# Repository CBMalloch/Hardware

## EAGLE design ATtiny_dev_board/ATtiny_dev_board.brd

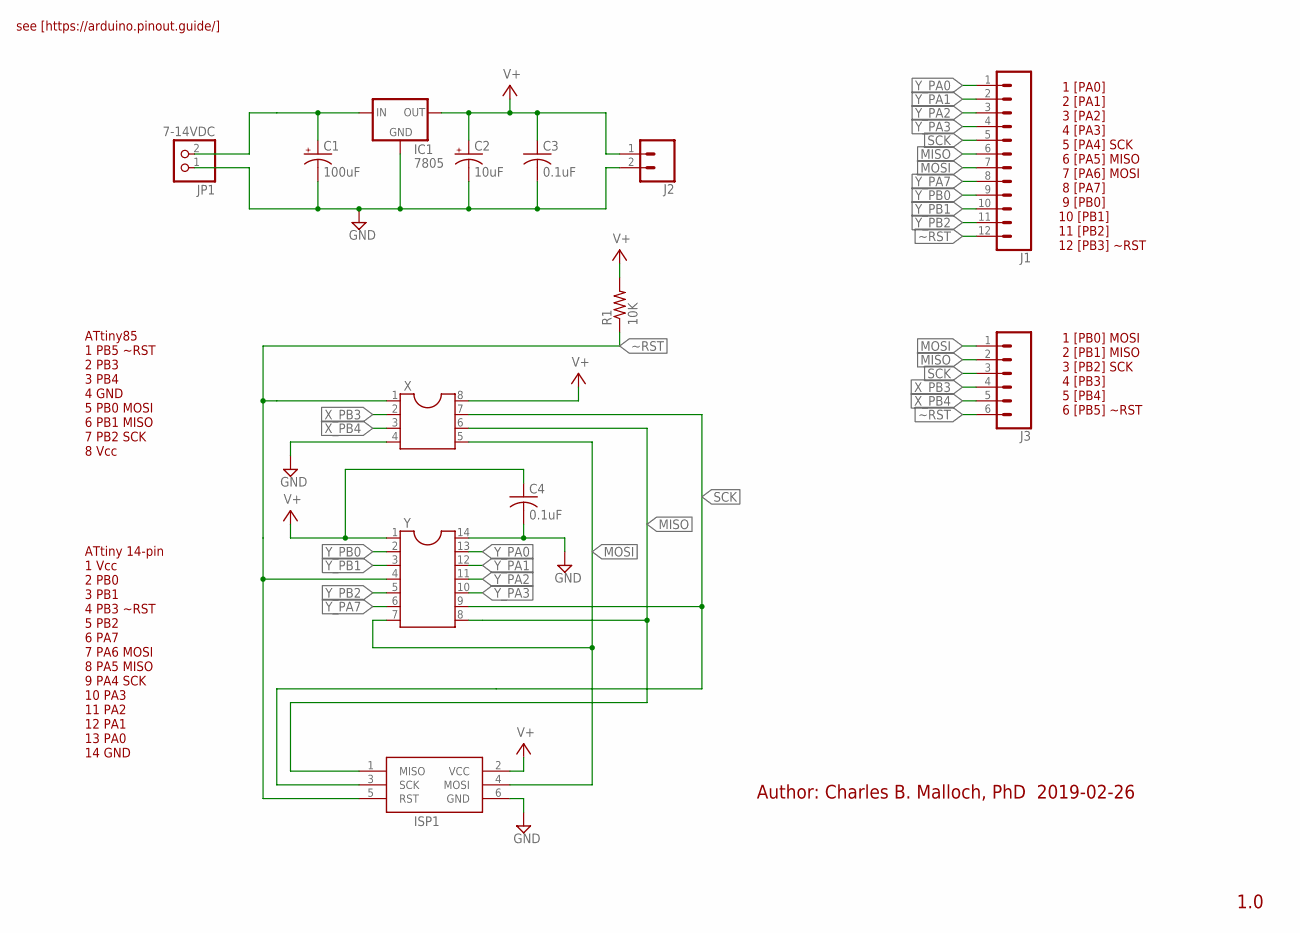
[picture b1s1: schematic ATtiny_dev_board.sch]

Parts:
C1: 100uF; TT2D7
C2: 10uF; E1,8-4
C3, C4: 0.1uF; C025-025X050
IC1: 7805; TO-220-ALT
ISP1: AVRISP-BOX
J1: CONN_12LOCK_LONGPADS; 1X12_LOCK_LONGPADS
J2: CONN_02LOCK_LONGPADS; 1X02_LOCK_LONGPADS
J3: CONN_06LOCK_LONGPADS; 1X06_LOCK_LONGPADS
JP1: 7-14VDC; 1X02
R1: 10K; 0309/12
X: DIL8S; SOCKET-08
Y: DIL14S; SOCKET-14

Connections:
5VDC: C2.+, C3.1, C4.1, IC1.OUT, ISP1.2 (VCC), J2.1, R1.2, X.8, Y.1
GND: C1.-, C2.-, C3.2, C4.2, IC1.GND, ISP1.6 (GND), J2.2, JP1.1, X.4, Y.14
MISO: ISP1.1 (MISO), J1.6, J3.2, X.6, Y.8
MOSI: ISP1.4 (MOSI), J1.7, J3.1, X.5, Y.7
SCK: ISP1.3 (SCK), J1.5, J3.3, X.7, Y.9
VIN: C1.+, IC1.IN, JP1.2
X_PB3: J3.4, X.2
X_PB4: J3.5, X.3
Y_PA0: J1.1, Y.13
Y_PA1: J1.2, Y.12
Y_PA2: J1.3, Y.11
Y_PA3: J1.4, Y.10
Y_PA7: J1.8, Y.6
Y_PB0: J1.9, Y.2
Y_PB1: J1.10, Y.3
Y_PB2: J1.11, Y.5
~RST: ISP1.5 (RST), J1.12, J3.6, R1.1, X.1, Y.4

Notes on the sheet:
Author: Charles B. Malloch, PhD 2019-02-26
1.0
ATtiny85 1 PB5 ~RST 2 PB3 3 PB4 4 GND 5 PB0 MOSI 6 PB1 MISO 7 PB2 SCK 8 Vcc
see [https://arduino.pinout.guide/]
ATtiny 14-pin 1 Vcc 2 PB0 3 PB1 4 PB3 ~RST 5 PB2 6 PA7 7 PA6 MOSI 8 PA5 MISO 9 PA4 SCK 10 PA3 11 PA2 12 PA1 13 PA0 14 GND
1 [PB0] MOSI 2 [PB1] MISO 3 [PB2] SCK 4 [PB3] 5 [PB4] 6 [PB5] ~RST
1 [PA0] 2 [PA1] 3 [PA2] 4 [PA3] 5 [PA4] SCK 6 [PA5] MISO 7 [PA6] MOSI 8 [PA7] 9 [PB0] 10 [PB1] 11 [PB2] 12 [PB3] ~RST

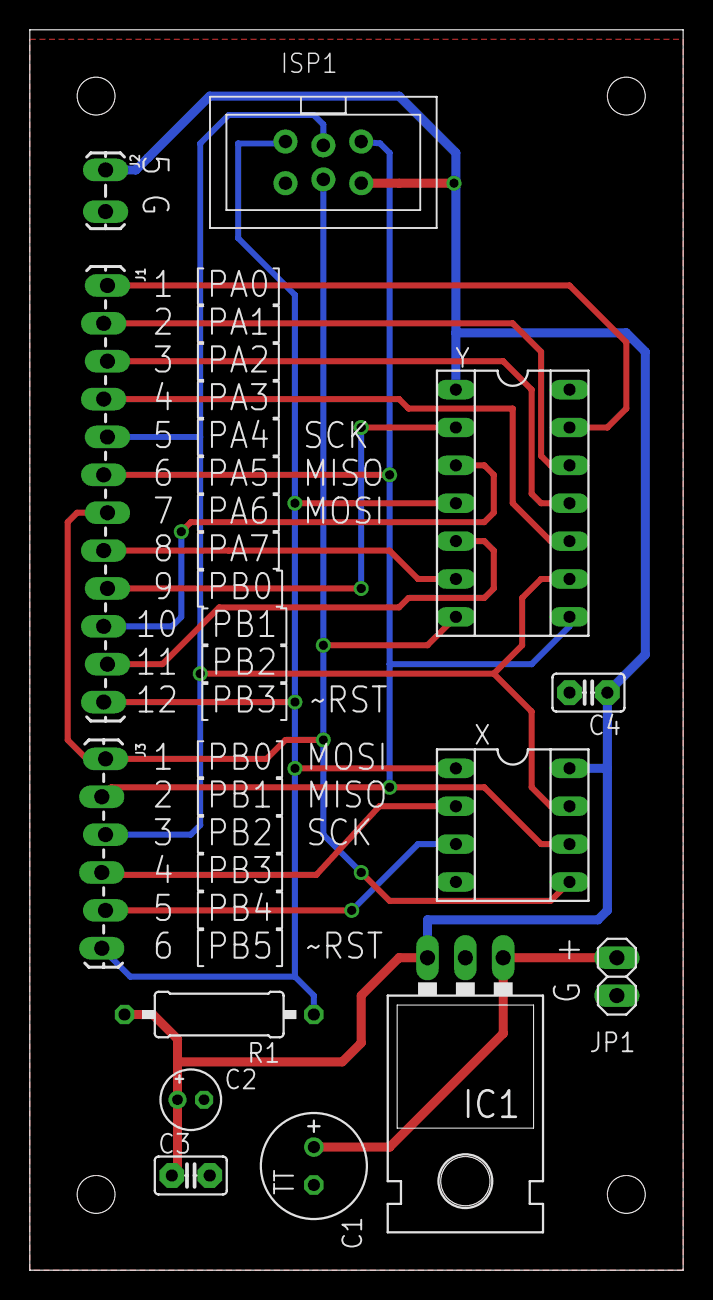
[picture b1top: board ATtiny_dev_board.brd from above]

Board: 2 copper layers, 43.8 x 83.2 mm, 13 parts (0 on the bottom side), 17 nets.

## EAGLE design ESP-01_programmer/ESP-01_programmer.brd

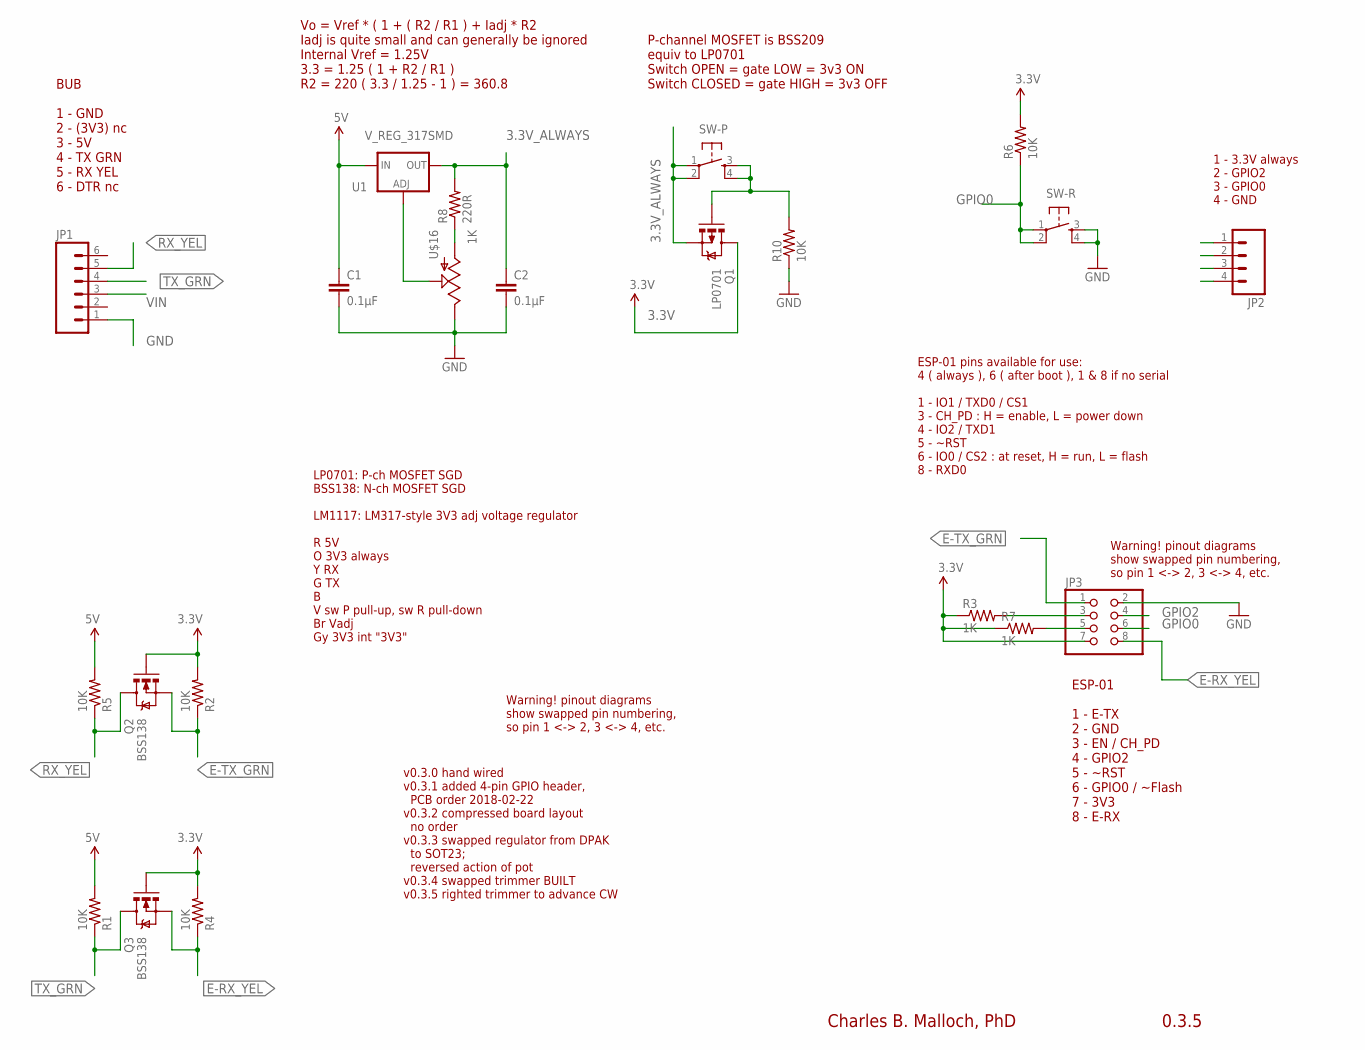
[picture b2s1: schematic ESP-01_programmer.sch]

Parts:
C1, C2: 0.1µF; 1206
JP1: M06LOCK_LONGPADS; 1X06_LOCK_LONGPADS
JP2: M04LOCK_LONGPADS; 1X04_LOCK_LONGPADS
JP3: PINHD-2X4; 2X04
Q1: LP0701; SOT23-3
Q2, Q3: BSS138; SOT23-3
R1, R2, R4, R5, R6, R10: 10K; 1206
R3, R7: 1K; 1206
R8: 220R; 1206
SW-P: TAC_SWITCHPTH; TACTILE-PTH
SW-R: TAC_SWITCHPTH; TACTILE-PTH
U1: V_REG_317SMD; SOT223
U$16: 1K; 3362U

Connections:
3.3V: JP3.7, Q1.3 (D), Q2.1 (G), Q3.1 (G), R2.2, R3.1, R4.2, R6.2, R7.1
3.3V_ALWAYS: C2.1, JP2.1, Q1.2 (S), R8.2, SW-P.1, SW-P.2, U1.2 (OUT)
E-RX_YEL: JP3.8, Q3.2 (S), R4.1
E-TX_GRN: JP3.1, Q2.2 (S), R2.1
GND: C1.2, C2.2, JP1.1, JP2.4, JP3.2, R10.1, SW-R.3, SW-R.4, U$16.P$1 (E)
GPIO0: JP2.3, JP3.6, R6.1, SW-R.1, SW-R.2
GPIO2: JP2.2, JP3.4
unnamed: JP3.3, R3.2
unnamed: JP3.5, R7.2
unnamed: R8.1, U$16.P$3 (A)
unnamed: U1.1 (ADJ), U$16.P$2 (S)
unnamed: Q1.1 (G), R10.2, SW-P.3, SW-P.4
RX_YEL: JP1.5, Q2.3 (D), R5.1
TX_GRN: JP1.4, Q3.3 (D), R1.1
VIN: C1.1, JP1.3, R1.2, R5.2, U1.3 (IN)

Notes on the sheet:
BUB 1 - GND 2 - (3V3) nc 3 - 5V 4 - TX GRN 5 - RX YEL 6 - DTR nc
Charles B. Malloch, PhD
0.3.5
ESP-01 1 - E-TX 2 - GND 3 - EN / CH_PD 4 - GPIO2 5 - ~RST 6 - GPIO0 / ~Flash 7 - 3V3 8 - E-RX
LP0701: P-ch MOSFET SGD BSS138: N-ch MOSFET SGD LM1117: LM317-style 3V3 adj voltage regulator R 5V O 3V3 always Y RX G TX B V sw P pull-up, sw R pull-down Br Vadj Gy 3V3 int "3V3"
ESP-01 pins available for use: 4 ( always ), 6 ( after boot ), 1 & 8 if no serial 1 - IO1 / TXD0 / CS1 3 - CH_PD : H = enable, L = power down 4 - IO2 / TXD1 5 - ~RST 6 - IO0 / CS2 : at reset, H = run, L = flash 8 - RXD0
1 - 3.3V always 2 - GPIO2 3 - GPIO0 4 - GND
v0.3.0 hand wired v0.3.1 added 4-pin GPIO header, PCB order 2018-02-22 v0.3.2 compressed board layout no order v0.3.3 swapped regulator from DPAK to SOT23; reversed action of pot v0.3.4 swapped trimmer BUILT v0.3.5 righted trimmer to advance CW
P-channel MOSFET is BSS209 equiv to LP0701 Switch OPEN = gate LOW = 3v3 ON Switch CLOSED = gate HIGH = 3v3 OFF
Warning! pinout diagrams show swapped pin numbering, so pin 1 <-> 2, 3 <-> 4, etc.
Vo = Vref * ( 1 + ( R2 / R1 ) + Iadj * R2 Iadj is quite small and can generally be ignored Internal Vref = 1.25V 3.3 = 1.25 ( 1 + R2 / R1 ) R2 = 220 ( 3.3 / 1.25 - 1 ) = 360.8

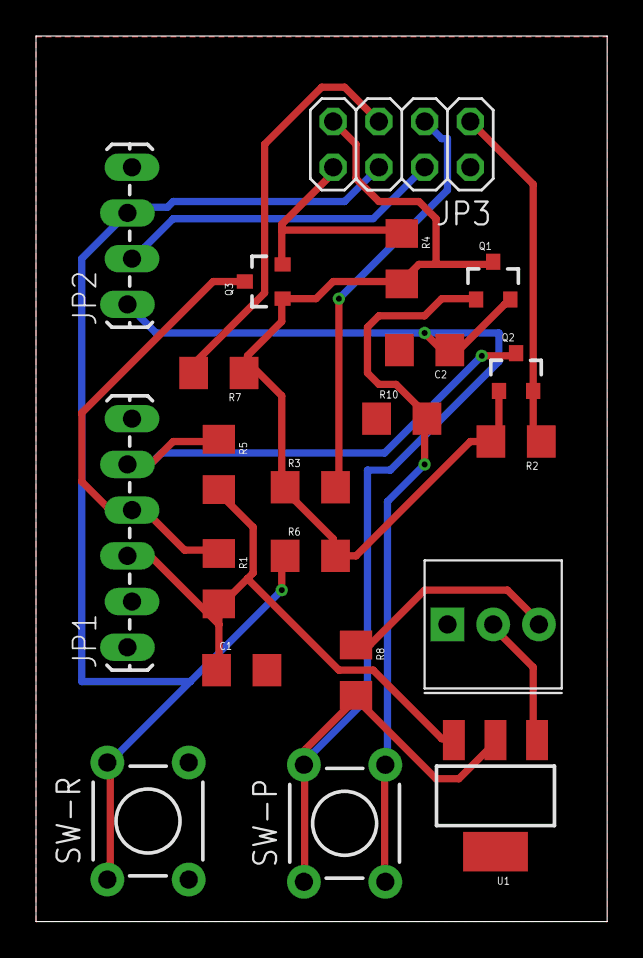
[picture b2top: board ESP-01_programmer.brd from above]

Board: 2 copper layers, 31.7 x 49.2 mm, 21 parts (0 on the bottom side), 15 nets.

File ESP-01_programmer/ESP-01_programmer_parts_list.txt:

Partlist exported from /Users/chuck/Documents/Develop/eagle/ESP-01_programmer/ESP-01_programmer.sch at 2018-02-24 10:13 AM

Part Value          Device             Package            Description       PROD_ID     VALUE 
C1   0.1µF          CAP1206            1206               Capacitor                           
C2   0.1µF          CAP1206            1206               Capacitor                           
JP1                 M06LOCK_LONGPADS   1X06_LOCK_LONGPADS Header 6                            
JP2                 M04LOCK_LONGPADS   1X04_LOCK_LONGPADS Header 4                            
JP3                 PINHD-2X4          2X04               PIN HEADER                          
Q1   LP0701         MOSFET-PCHANNELSMD SOT23-3            Generic PMOSFET                     
Q2   BSS138         BSS138TRANS-00830  SOT23-3            NMOSFET, Enh Mode TRANS-00830 BSS138
Q3   BSS138         BSS138TRANS-00830  SOT23-3            NMOSFET, Enh Mode TRANS-00830 BSS138
R1   10K            RESISTOR1206       1206               Resistor                            
R2   10K            RESISTOR1206       1206               Resistor                            
R3   1K             RESISTOR1206       1206               Resistor                            
R4   10K            RESISTOR1206       1206               Resistor                            
R5   10K            RESISTOR1206       1206               Resistor                            
R6   10K            RESISTOR1206       1206               Resistor                            
R7   1K             RESISTOR1206       1206               Resistor                            
R8   220R           RESISTOR1206       1206               Resistor                            
R10  10K            RESISTOR1206       1206               Resistor                            
SW-P                TAC_SWITCHPTH      TACTILE-PTH        Momentary Switch                    
SW-R                TAC_SWITCHPTH      TACTILE-PTH        Momentary Switch                    
U$16 100R           POT                ALPS_POT                                               
U1   V_REG_317DPACK V_REG_317DPACK     V-REG_DPACK        Voltage Regulator

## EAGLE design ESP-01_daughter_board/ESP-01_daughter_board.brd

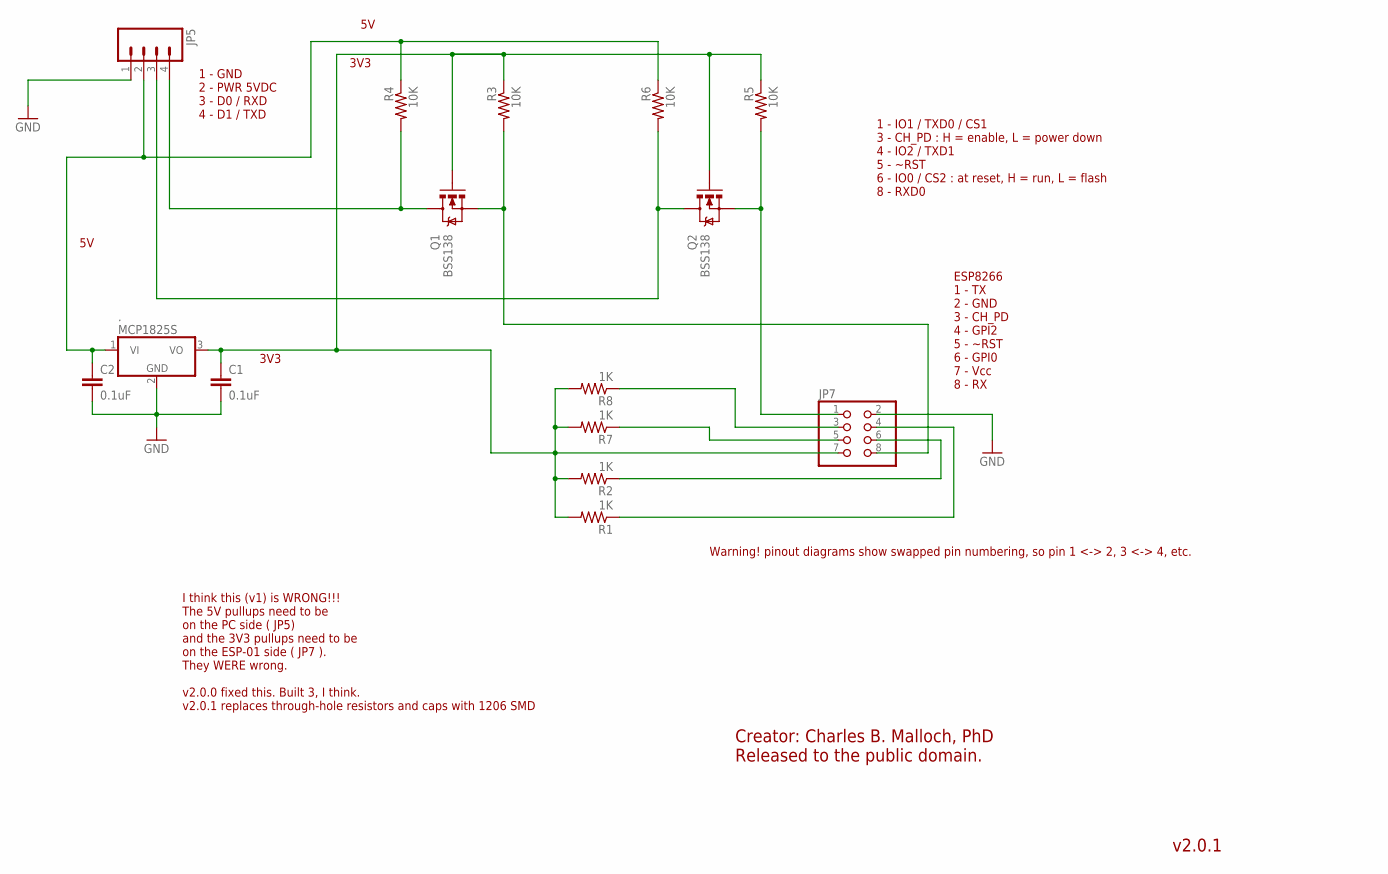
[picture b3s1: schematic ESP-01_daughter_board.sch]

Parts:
.: MCP1825S; SOT223
C1, C2: 0.1uF; C1206
JP5: M04LOCK_LONGPADS; 1X04_LOCK_LONGPADS
JP7: PINHD-2X4; 2X04
Q1, Q2: BSS138; SOT23-3
R1, R2, R7, R8: 1K; M1206
R3, R4, R5, R6: 10K; 1206

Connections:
3V3: ..3 (VO), C1.1, JP7.7, Q1.1 (G), Q2.1 (G), R1.2, R2.2, R3.1, R5.1, R7.2, R8.2
5V: ..1 (VI), C2.1, JP5.2, R4.1, R6.1
E-RX: JP7.8, Q1.2 (S), R3.2
E-TX: JP7.1, Q2.2 (S), R5.2
GND: ..2 (GND), C1.2, C2.2, JP5.1, JP7.2
unnamed: JP7.3, R8.1
unnamed: JP7.5, R7.1
unnamed: JP7.6, R2.1
unnamed: JP7.4, R1.1
RX: JP5.3, Q2.3 (D), R6.2
TX: JP5.4, Q1.3 (D), R4.2

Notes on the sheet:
v2.0.1
Creator: Charles B. Malloch, PhD Released to the public domain.
1 - GND 2 - PWR 5VDC 3 - D0 / RXD 4 - D1 / TXD
ESP8266 1 - TX 2 - GND 3 - CH_PD 4 - GPI2 5 - ~RST 6 - GPI0 7 - Vcc 8 - RX
3V3
I think this (v1) is WRONG!!! The 5V pullups need to be on the PC side ( JP5) and the 3V3 pullups need to be on the ESP-01 side ( JP7 ). They WERE wrong. v2.0.0 fixed this. Built 3, I think. v2.0.1 replaces through-hole resistors and caps with 1206 SMD
1 - IO1 / TXD0 / CS1 3 - CH_PD : H = enable, L = power down 4 - IO2 / TXD1 5 - ~RST 6 - IO0 / CS2 : at reset, H = run, L = flash 8 - RXD0
Warning! pinout diagrams show swapped pin numbering, so pin 1 <-> 2, 3 <-> 4, etc.

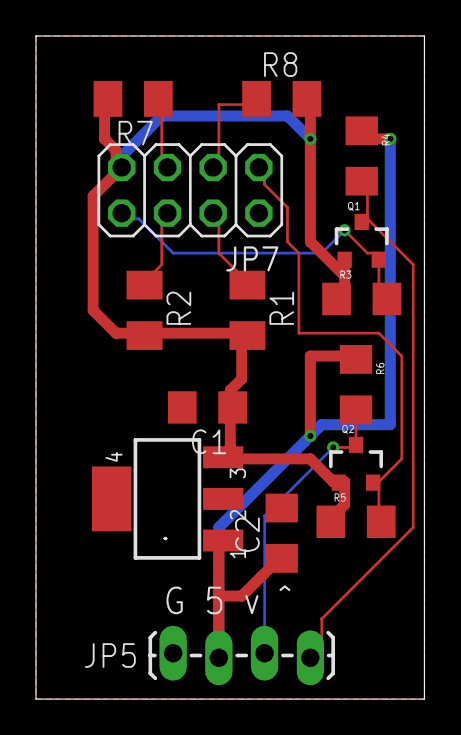
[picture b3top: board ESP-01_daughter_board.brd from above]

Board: 2 copper layers, 21.6 x 36.8 mm, 15 parts (0 on the bottom side), 11 nets.

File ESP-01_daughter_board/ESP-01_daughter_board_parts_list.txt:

Partlist exported from /Users/chuck/Documents/Develop/eagle/ESP-01_daughter_board/ESP-01_daughter_board.sch at 2018-02-24 10:28 AM

Part Value    Device            Package            Description                                      PROD_ID     SPICEMODEL SPICEPREFIX VALUE 
.    MCP1825S MCP1703DB         SOT223             250 mA, 16V, Low Quiescent Current LDO Regulator                                          
C1   0.1uF    CC1206            C1206              CAPACITOR, European symbol                                   NONE       C                 
C2   0.1uF    CC1206            C1206              CAPACITOR, European symbol                                   NONE       C                 
JP5           M04LOCK_LONGPADS  1X04_LOCK_LONGPADS Header 4                                                                                  
JP7           PINHD-2X4         2X04               PIN HEADER                                                                                
Q1   BSS138   BSS138TRANS-00830 SOT23-3            NMOSFET, Enh Mode                                TRANS-00830                        BSS138
Q2   BSS138   BSS138TRANS-00830 SOT23-3            NMOSFET, Enh Mode                                TRANS-00830                        BSS138
R1   1K       R-US_M1206        M1206              RESISTOR, American symbol                                                                 
R2   1K       R-US_M1206        M1206              RESISTOR, American symbol                                                                 
R3   10K      RESISTOR1206      1206               Resistor                                                                                  
R4   10K      RESISTOR1206      1206               Resistor                                                                                  
R5   10K      RESISTOR1206      1206               Resistor                                                                                  
R6   10K      RESISTOR1206      1206               Resistor                                                                                  
R7   1K       R-US_M1206        M1206              RESISTOR, American symbol                                                                 
R8   1K       R-US_M1206        M1206              RESISTOR, American symbol

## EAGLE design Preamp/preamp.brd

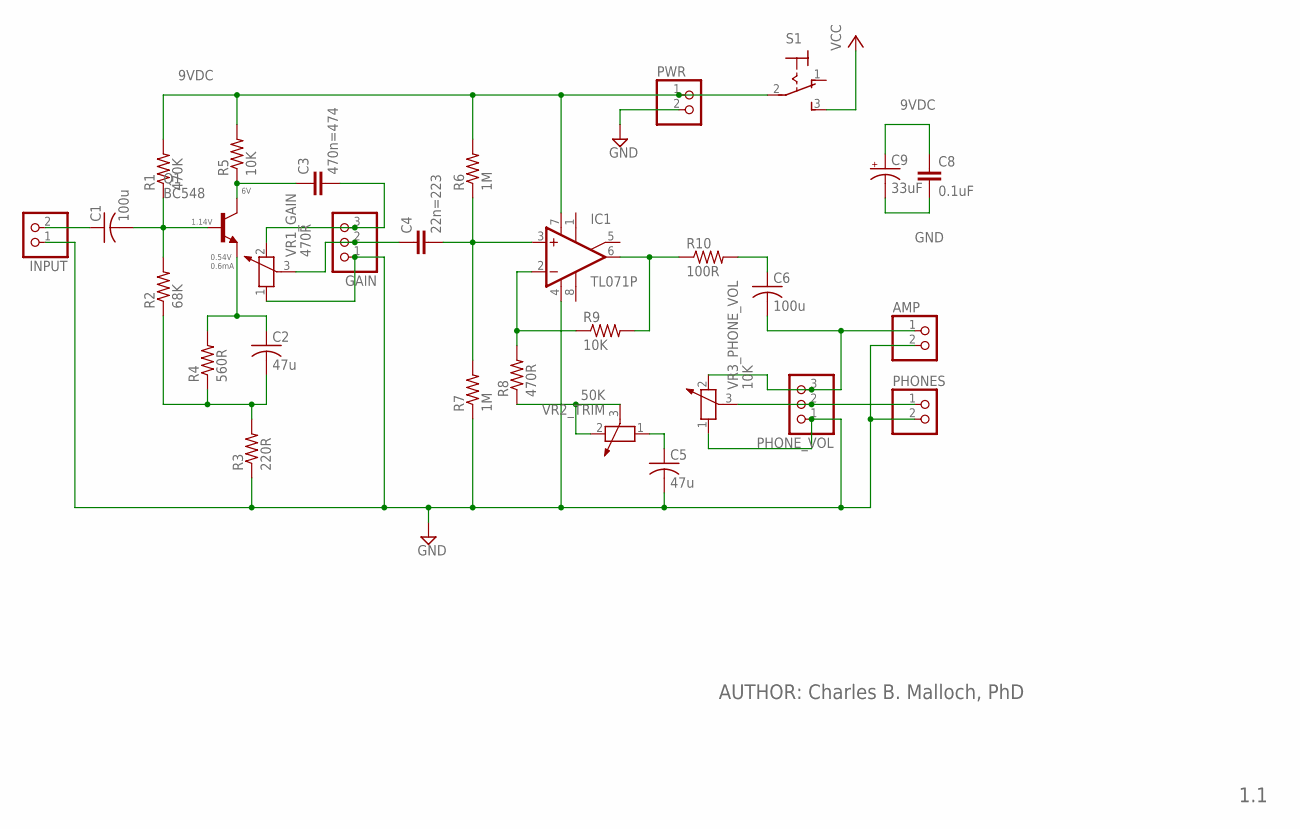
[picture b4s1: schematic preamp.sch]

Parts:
AMP: PINHD-1X2; 1X02
C1, C6: 100u; C025-040X050
C2, C5: 47u; C025-040X050
C3: 470n=474; C025-060X050
C4: 22n=223; C025-060X050
C8: 0.1uF; C025-030X050
C9: 33uF; E5-6
GAIN: PINHD-1X3; 1X03
IC1: TL071P; DIL08
INPUT: PINHD-1X2; 1X02
PHONES: PINHD-1X2; 1X02
PHONE_VOL: PINHD-1X3; 1X03
PWR: PINHD-1X2; 1X02
Q1: BC548; TO92-EBC
R1: 470K; 0204/7
R2: 68K; 0204/7
R3: 220R; 0204/7
R4: 560R; 0204/7
R5, R9: 10K; 0204/7
R6, R7: 1M; 0204/7
R8: 470R; 0204/7
R10: 100R; 0204/7
S1: 320-916
VR1_GAIN: 470R; PT-10
VR2_TRIM: 50K; PT-10
VR3_PHONE_VOL: 10K; PT-10

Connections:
9VDC: C8.1, C9.+, IC1.7 (V+), PWR.1, R1.2, R5.2, R6.2, S1.2
BAT+: S1.3 (S)
GND: AMP.2, C5.2, C8.2, C9.-, GAIN.1, IC1.4 (V-), INPUT.1, PHONES.2, PHONE_VOL.1, PWR.2, R3.1, R7.1, VR1_GAIN.1, VR3_PHONE_VOL.1
unnamed: C4.1, GAIN.2, VR1_GAIN.3
unnamed: C1.1, INPUT.2
unnamed: C1.2, Q1.B, R1.1, R2.2
unnamed: C3.2, GAIN.3, VR1_GAIN.2
unnamed: PHONES.1, PHONE_VOL.2, VR3_PHONE_VOL.3
unnamed: C3.1, Q1.C, R5.1
unnamed: C2.2, R2.1, R3.2, R4.1
unnamed: C4.2, IC1.3 (+IN), R6.1, R7.2
unnamed: C2.1, Q1.E, R4.2
unnamed: IC1.6 (OUT), R9.2, R10.1
unnamed: IC1.2 (-IN), R8.2, R9.1
unnamed: R8.1, VR2_TRIM.2, VR2_TRIM.3
unnamed: C5.1, VR2_TRIM.1
unnamed: C6.1, R10.2
unnamed: AMP.1, C6.2, PHONE_VOL.3, VR3_PHONE_VOL.2

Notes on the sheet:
AUTHOR: Charles B. Malloch, PhD
1.1
1.14V
0.54V 0.6mA

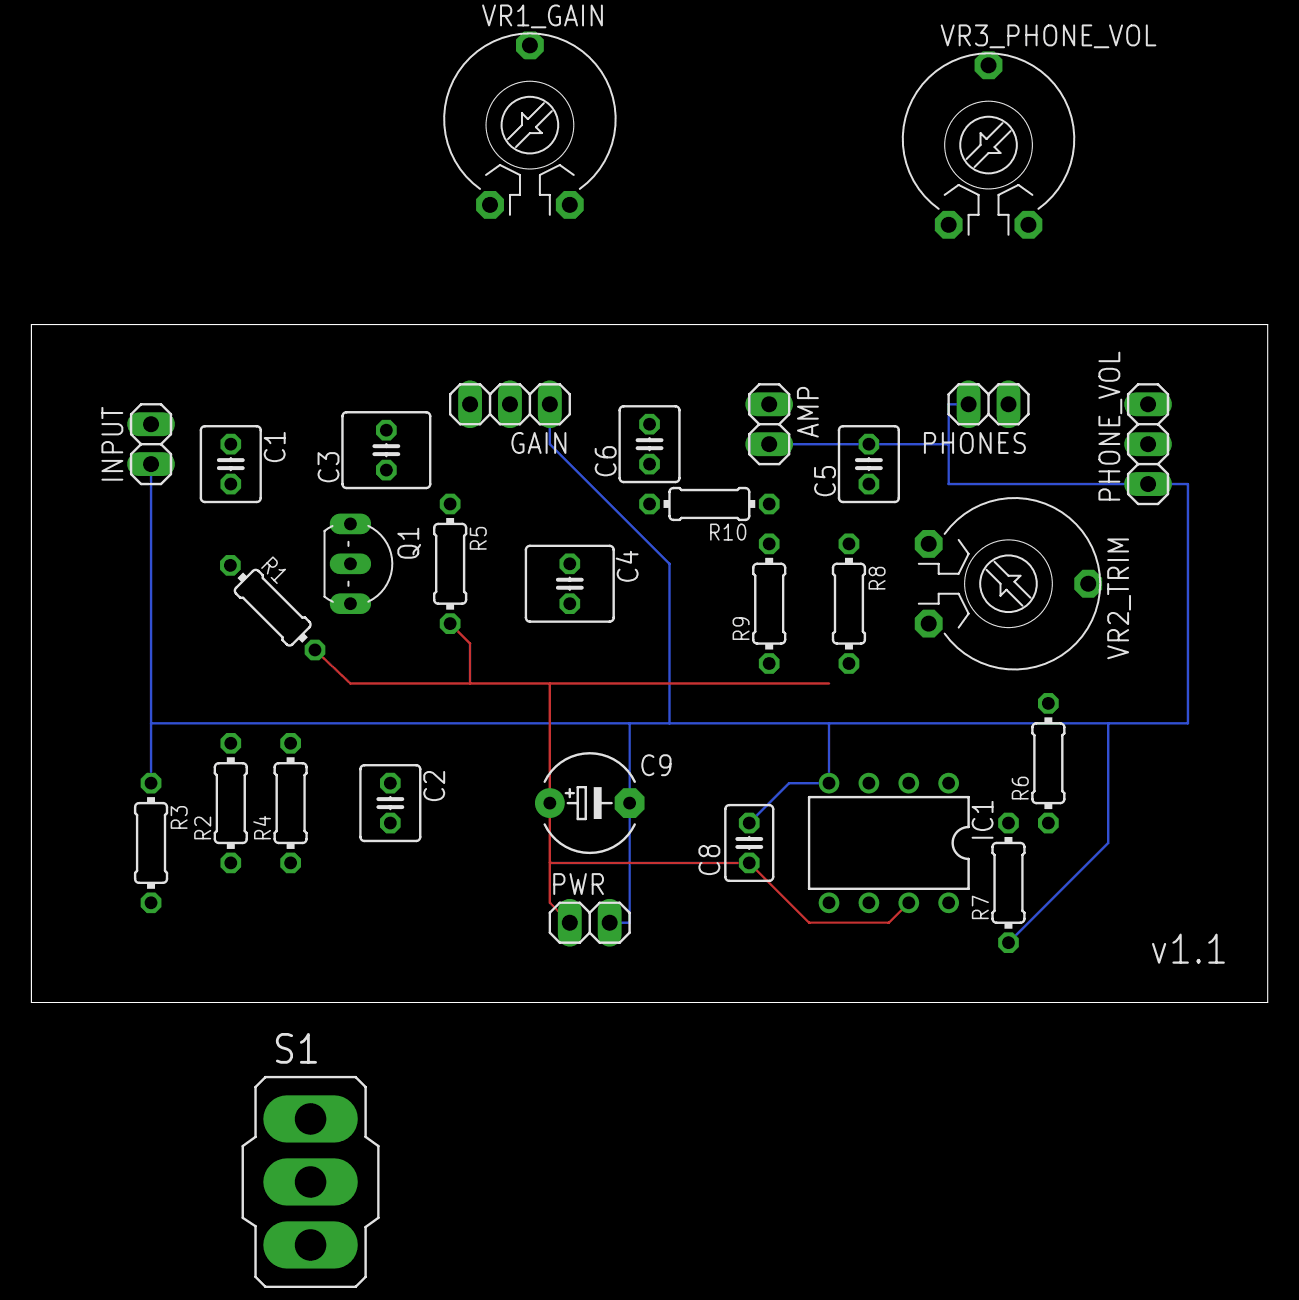
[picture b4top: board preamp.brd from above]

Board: 2 copper layers, 78.7 x 43.2 mm, 30 parts (0 on the bottom side), 17 nets.

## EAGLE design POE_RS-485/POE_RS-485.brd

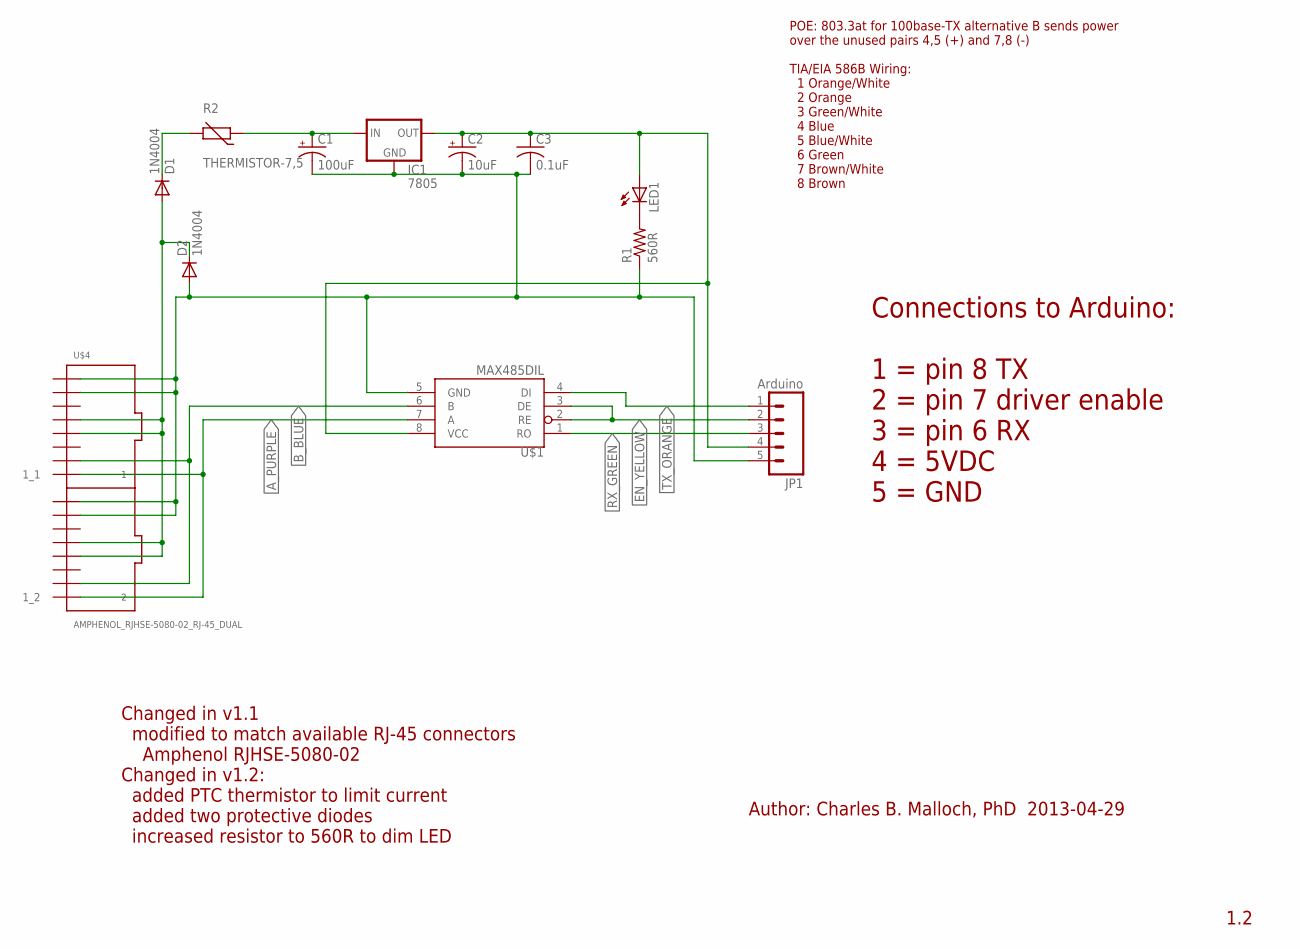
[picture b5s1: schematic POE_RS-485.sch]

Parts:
C1: 100uF; TT2D7
C2: 10uF; E1,8-4
C3: 0.1uF; C025-025X050
D1, D2: 1N4004; DO41-10
IC1: 7805; TO-220-ALT
JP1: Arduino; 1X05_LOCK_LONGPADS
LED1: LED3MM
R1: 560R; 0204/7
R2: THERMISTOR-7,5; R-7,5
U$1: MAX485DIL; DIL08
U$4: AMPHENOL_RJHSE-5080-02_RJ-45_DUAL; AMPHENOL_RJHSE-5080-02

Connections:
A_PURPLE: U$1.7 (A), U$4.TX_D1+_2 (1_2), U$4.TX_DI+_1 (1_1)
B_BLUE: U$1.6 (B), U$4.TX_D1-_2 (2_2), U$4.TX_DI-_1 (2_1)
EN_YELLOW: JP1.2, U$1.2 (RE), U$1.3 (DE)
GND: C1.-, C2.-, C3.2, D2.A, IC1.GND, JP1.5, R1.1, U$1.5 (GND), U$4.POE-_1_1 (7_1), U$4.POE-_1_2 (7_2), U$4.POE-_2_1 (8_1), U$4.POE-_2_2 (8_2)
unnamed: LED1.K (C), R1.2
unnamed: C1.+, IC1.IN, R2.1
unnamed: D1.C, R2.2
PWR: C2.+, C3.1, IC1.OUT, JP1.4, LED1.A, U$1.8 (VCC)
RX_GREEN: JP1.3, U$1.1 (RO)
TX_ORANGE: JP1.1, U$1.4 (DI)
VIN: D1.A, D2.C, U$4.POE+_1_1 (4_1), U$4.POE+_1_2 (4_2), U$4.POE+_2_1 (5_1), U$4.POE+_2_2 (5_2)

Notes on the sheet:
Author: Charles B. Malloch, PhD 2013-04-29
1.2
Connections to Arduino: 1 = pin 8 TX 2 = pin 7 driver enable 3 = pin 6 RX 4 = 5VDC 5 = GND
POE: 803.3at for 100base-TX alternative B sends power over the unused pairs 4,5 (+) and 7,8 (-) TIA/EIA 586B Wiring: 1 Orange/White 2 Orange 3 Green/White 4 Blue 5 Blue/White 6 Green 7 Brown/White 8 Brown
Changed in v1.1 modified to match available RJ-45 connectors Amphenol RJHSE-5080-02 Changed in v1.2: added PTC thermistor to limit current added two protective diodes increased resistor to 560R to dim LED

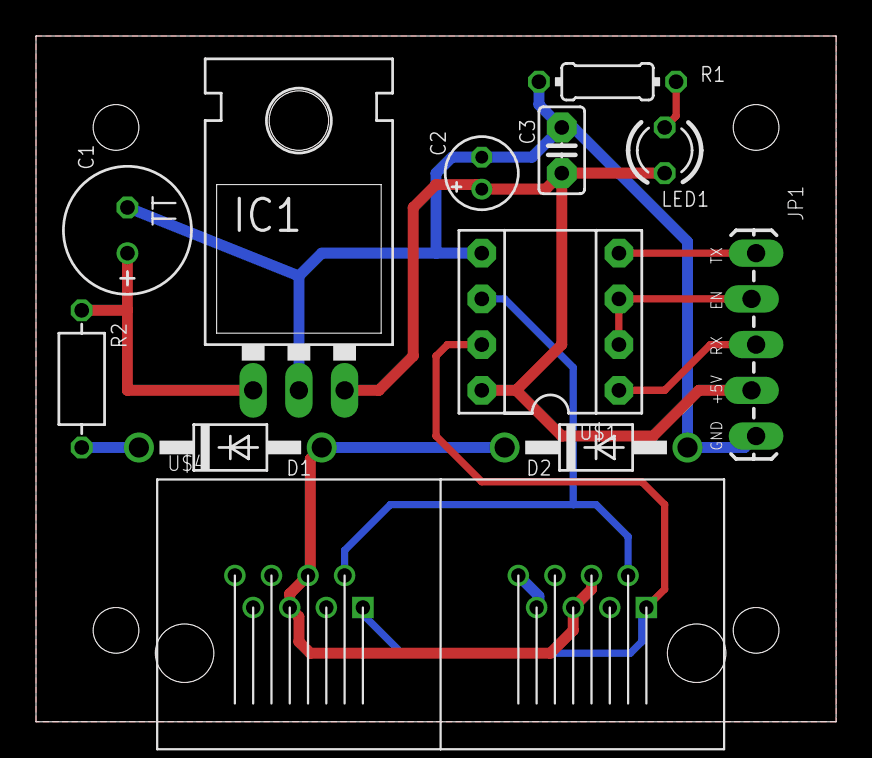
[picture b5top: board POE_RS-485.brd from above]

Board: 2 copper layers, 44.5 x 38.1 mm, 12 parts (0 on the bottom side), 11 nets.

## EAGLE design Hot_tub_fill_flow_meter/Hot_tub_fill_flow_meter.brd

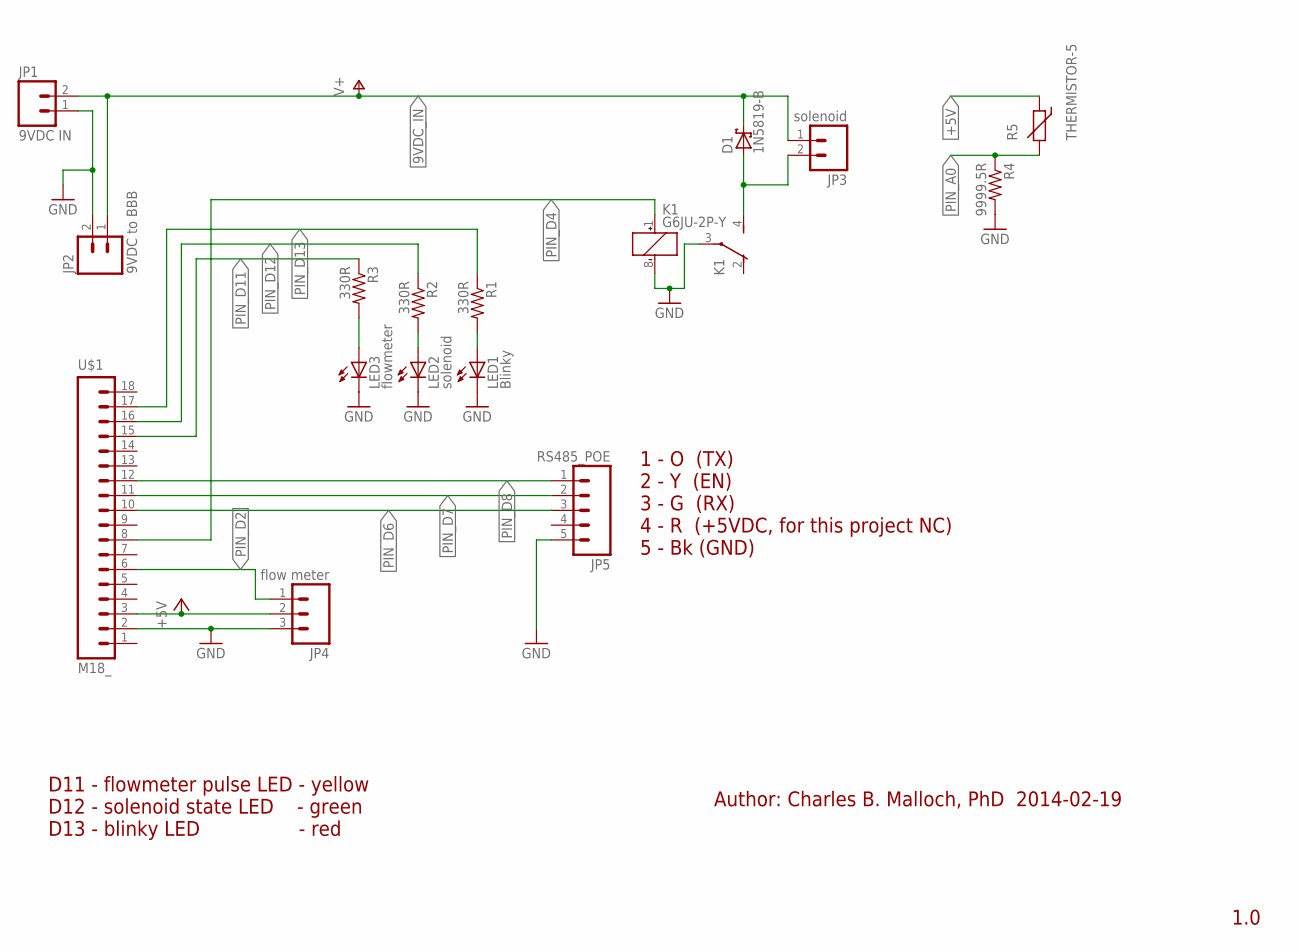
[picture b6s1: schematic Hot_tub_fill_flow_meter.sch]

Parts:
D1: 1N5819-B; DO41-7.6
JP1: 9VDC IN; 1X02_LOCK
JP2: 9VDC to BBB; 1X02_LOCK
JP3: solenoid; 1X02_LOCK
JP4: flow meter; 1X03_LOCK
JP5: RS485_POE; 1X05
K1: G6JU-2P-Y; G6J-2P-Y
LED1: Blinky; LED5MM
LED2: solenoid; LED5MM
LED3: flowmeter; LED5MM
R1, R2, R3: 330R; AXIAL-0.3
R4: 9999.5R; AXIAL-0.3
R5: THERMISTOR-5; R-5
U$1: M18_; 1X18

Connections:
9VDC_IN: D1.C, JP1.2, JP2.1, JP3.1
+5V: JP4.2, R5.1, U$1.3
GND: JP1.1, JP2.2, JP4.3, JP5.5, K1.3, K1.8 (-), LED1.K (C), LED2.K (C), LED3.K (C), R4.P$2 (2), U$1.2
unnamed: LED1.A, R1.P$2 (2)
unnamed: D1.A, JP3.2, K1.4 (S)
unnamed: LED2.A, R2.P$2 (2)
unnamed: LED3.A, R3.P$2 (2)
PIN_A0: R4.P$1 (1), R5.2
PIN_D2: JP4.1, U$1.6
PIN_D4: K1.1 (+), U$1.8
PIN_D6: JP5.3, U$1.10
PIN_D7: JP5.2, U$1.11
PIN_D8: JP5.1, U$1.12
PIN_D11: R3.P$1 (1), U$1.15
PIN_D12: R2.P$1 (1), U$1.16
PIN_D13: R1.P$1 (1), U$1.17

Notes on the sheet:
Author: Charles B. Malloch, PhD 2014-02-19
1.0
D11 - flowmeter pulse LED - yellow D12 - solenoid state LED - green D13 - blinky LED - red
1 - O (TX) 2 - Y (EN) 3 - G (RX) 4 - R (+5VDC, for this project NC) 5 - Bk (GND)

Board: 2 copper layers, 16 parts (0 on the bottom side), 16 nets, no tracks yet.

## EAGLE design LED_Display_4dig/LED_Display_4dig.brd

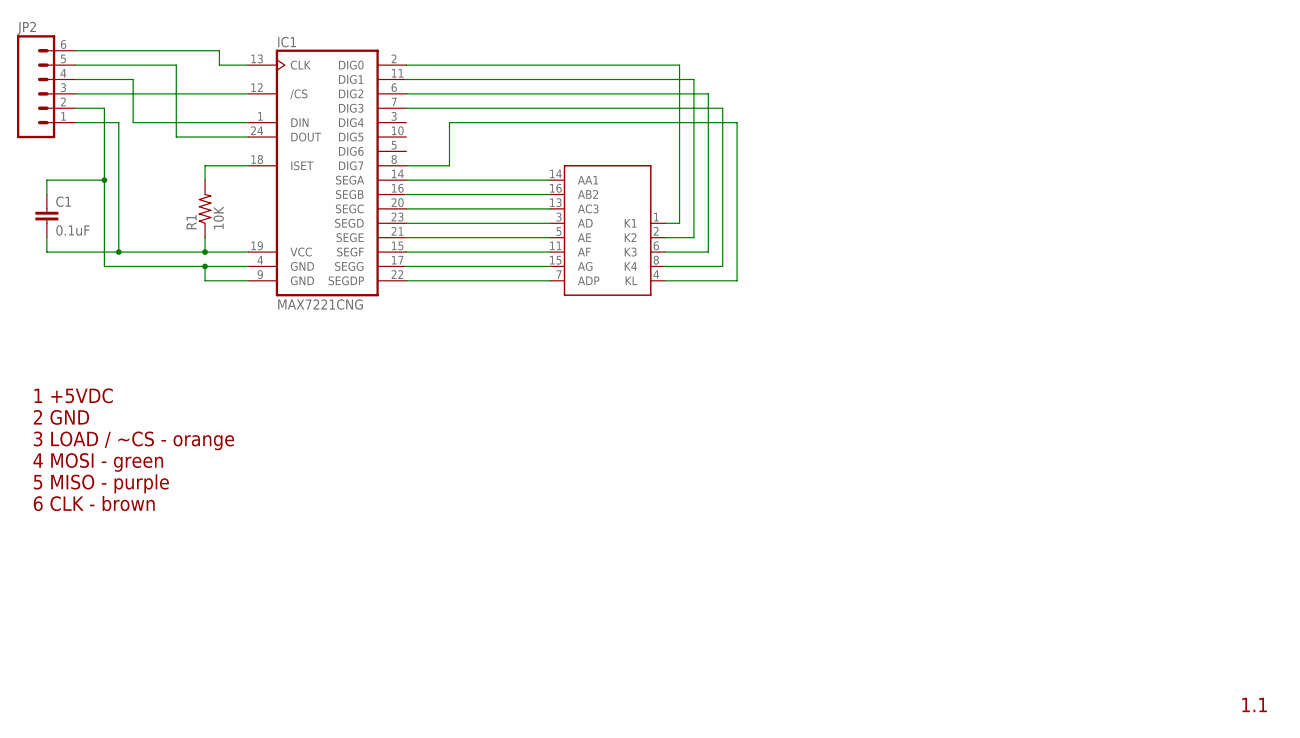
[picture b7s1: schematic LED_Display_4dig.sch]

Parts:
C1: 0.1uF; CAP-PTH-SMALL
IC1: MAX7221CNG; DIL24-3
JP2: M06LOCK_LONGPADS; 1X06_LOCK_LONGPADS
R1: 10K; AXIAL-0.4
U$1: LTC-4027JRLTC-4027JR; LTC-4727JR

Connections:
+5VDC: C1.2, IC1.19 (VCC), JP2.1, R1.P$1 (1)
GND: C1.1, IC1.4 (GND), IC1.9 (GND), JP2.2
unnamed: IC1.12 (/CS), JP2.3
unnamed: IC1.1 (DIN), JP2.4
unnamed: IC1.24 (DOUT), JP2.5
unnamed: IC1.13 (CLK), JP2.6
unnamed: IC1.2 (DIG0), U$1.1 (K1)
unnamed: IC1.11 (DIG1), U$1.2 (K2)
unnamed: IC1.6 (DIG2), U$1.6 (K3)
unnamed: IC1.7 (DIG3), U$1.8 (K4)
unnamed: IC1.8 (DIG7), U$1.4 (KL)
unnamed: IC1.14 (SEGA), U$1.14 (AA1)
unnamed: IC1.16 (SEGB), U$1.16 (AB2)
unnamed: IC1.20 (SEGC), U$1.13 (AC3)
unnamed: IC1.23 (SEGD), U$1.3 (AD)
unnamed: IC1.21 (SEGE), U$1.5 (AE)
unnamed: IC1.15 (SEGF), U$1.11 (AF)
unnamed: IC1.17 (SEGG), U$1.15 (AG)
unnamed: IC1.22 (SEGDP), U$1.7 (ADP)
unnamed: IC1.18 (ISET), R1.P$2 (2)

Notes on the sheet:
1 +5VDC 2 GND 3 LOAD / ~CS - orange 4 MOSI - green 5 MISO - purple 6 CLK - brown
1.1

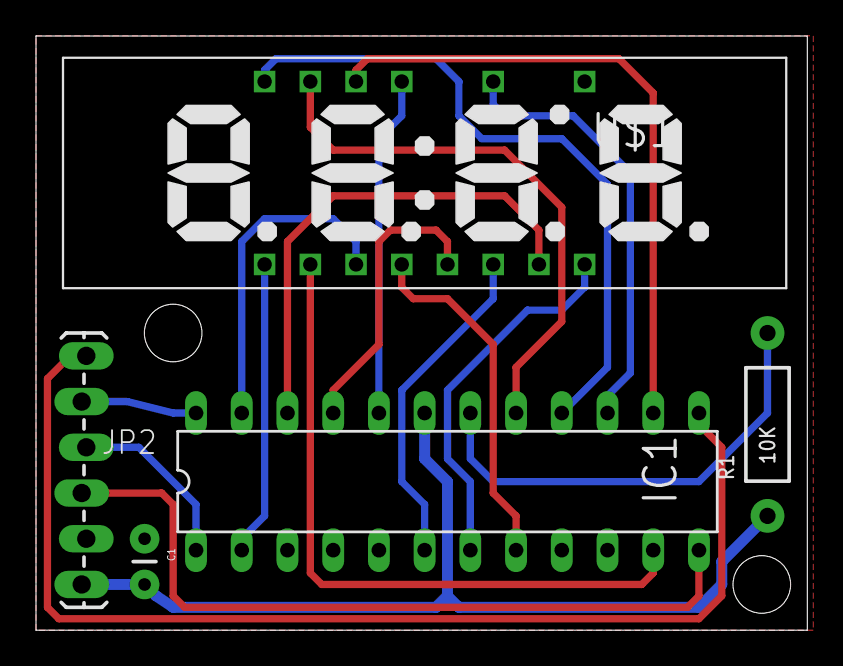
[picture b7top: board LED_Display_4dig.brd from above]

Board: 2 copper layers, 42.9 x 33.0 mm, 5 parts (0 on the bottom side), 20 nets.

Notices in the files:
ATtiny_dev_board/ATtiny_dev_board.brd:
© cbm electronics 2019
ESP-01_daughter_board/ESP-01_daughter_board.brd:
(c) 2018 cbm Electronics
ESP-01_programmer/ESP-01_programmer.brd:
© cbm Electronics 2018
parts and their libraries:
SparkFun-PowerIC: Licensing: CC v3.0 Share-Alike You are welcome to use this library for commercial purposes.
SparkFun-Connectors: Licensing: Creative Commons ShareAlike 4.0 International - https://creativecommons.org/licenses/by-sa/4.0
